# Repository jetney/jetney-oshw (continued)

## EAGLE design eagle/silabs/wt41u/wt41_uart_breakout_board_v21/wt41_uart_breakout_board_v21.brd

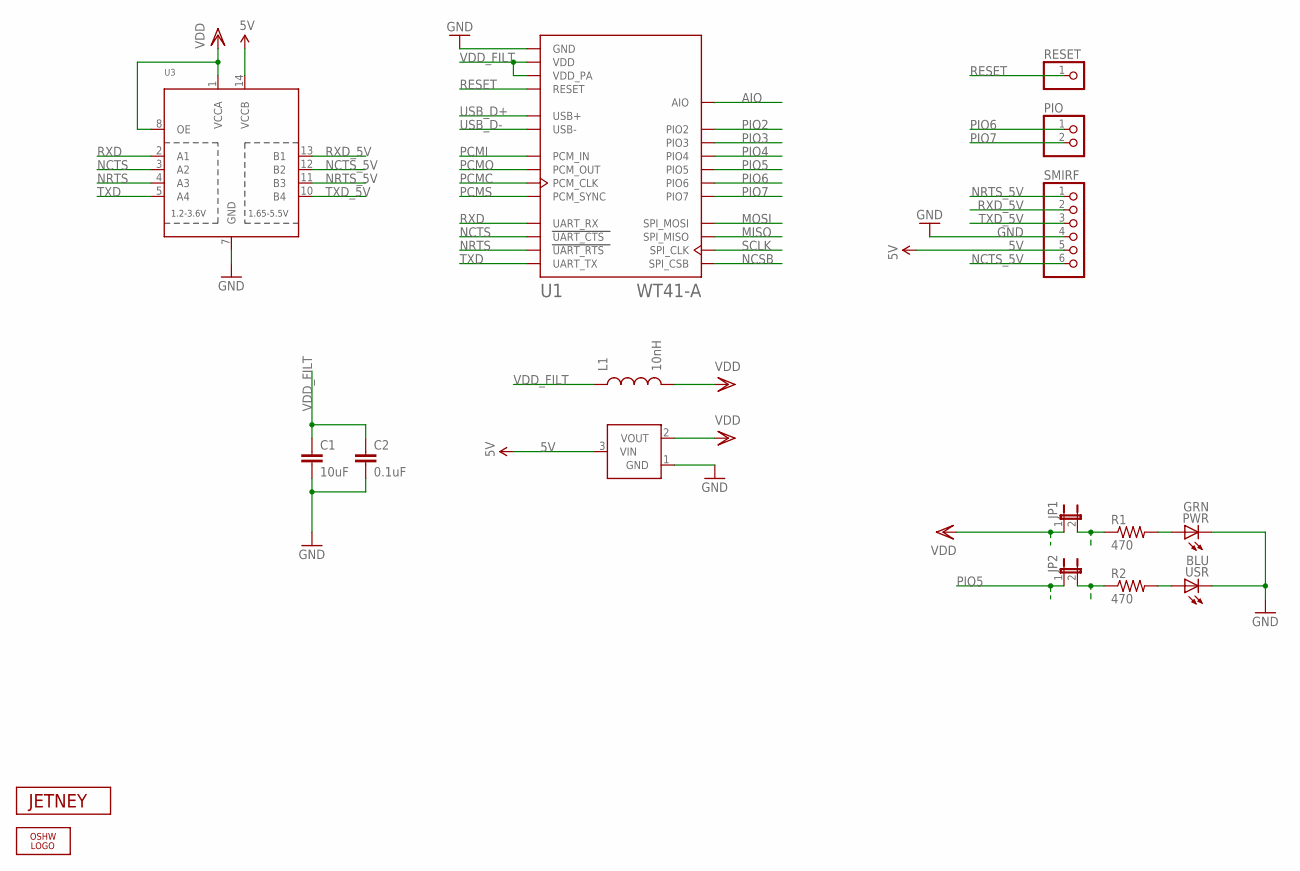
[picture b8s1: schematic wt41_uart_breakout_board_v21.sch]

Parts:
C1: 10uF; 0603-CAP
C2: 0.1uF; 0603-CAP
JP1, JP2: JUMPER-2SMD-NC; SJ_2S
L1: 10nH; 0603
LOGO1: OSHW_LOGO_FILLX0070-NT; OSHW_FILLX70_NOTEXT
PIO: PINHD-1X2; 1X02
PWR: GRN; CHIPLED_0805
R1, R2: 470; 0603-RES
RESET: PINHD-1X1; 1X01
SMIRF: PINHD-1X6; 1X06
U1: WT41-A
U2: MCP1700; SOT23-3
U3: TXB0104PWR; TSSOP14
U$4: JETNEY-LOGO-12
USR: BLU; CHIPLED_0805

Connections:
5V: SMIRF.5, U2.3 (VIN), U3.14 (VCCB)
AIO: U1.AIO
GND: C1.2, C2.2, PWR.C, SMIRF.4, U1.GND, U1.GND@2 (GND), U1.GND@3 (GND), U1.GND@4 (GND), U1.GND@5 (GND), U1.GND@6 (GND), U1.GND@7 (GND), U1.GND@8 (GND), U1.GND@9 (GND), U1.GND@10 (GND), U1.GND@11 (GND), U1.GND@12 (GND), U1.GND@13 (GND), U1.GND@14 (GND), U1.GND@15 (GND), U1.GND@16 (GND), U1.GND@17 (GND), U1.GND@18 (GND), U1.GND@19 (GND), U1.GND@20 (GND), U1.GND@21 (GND), U1.GND@22 (GND), U1.GND@23 (GND), U1.GND@24 (GND), U1.GND@25 (GND), U1.GND@26 (GND), U1.GND@27 (GND), U1.GND@28 (GND), U1.GND@29 (GND), U1.GND@30 (GND), U1.GND@31 (GND), U2.1 (GND), U3.7 (GND), USR.C
MISO: U1.SPI_MISO
MOSI: U1.SPI_MOSI
unnamed: PWR.A, R1.2
unnamed: R2.2, USR.A
unnamed: JP2.2, R2.1
NCSB: U1.SPI_CSB
NCTS: U1.UART_CTS, U3.3 (A2)
NCTS_5V: SMIRF.6, U3.12 (B2)
NRTS: U1.UART_RTS, U3.4 (A3)
NRTS_5V: SMIRF.1, U3.11 (B3)
PCMC: U1.PCM_CLK
PCMI: U1.PCM_IN
PCMO: U1.PCM_OUT
PCMS: U1.PCM_SYNC
PIO2: U1.PIO2
PIO3: U1.PIO3
PIO4: U1.PIO4
PIO5: JP2.1, U1.PIO5
PIO6: PIO.1, U1.PIO6
PIO7: PIO.2, U1.PIO7
RESET: RESET.1, U1.RESET
RXD: U1.UART_RX, U3.2 (A1)
RXD_5V: SMIRF.2, U3.13 (B1)
SCLK: U1.SPI_CLK
TXD: U1.UART_TX, U3.5 (A4)
TXD_5V: SMIRF.3, U3.10 (B4)
USB_D+: U1.USB+
USB_D-: U1.USB-
VDD: JP1.1, L1.2, U2.2 (VOUT), U3.1 (VCCA), U3.8 (OE)
VDDJP1: JP1.2, R1.1
VDD_FILT: C1.1, C2.1, L1.1, U1.VDD, U1.VDD_PA

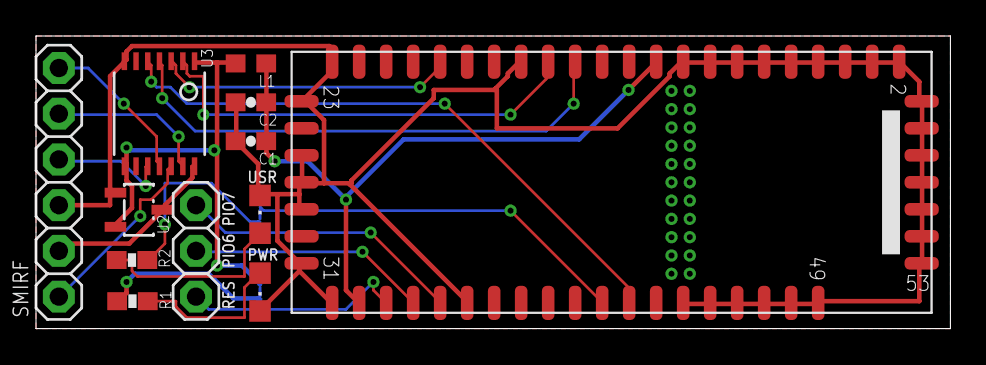
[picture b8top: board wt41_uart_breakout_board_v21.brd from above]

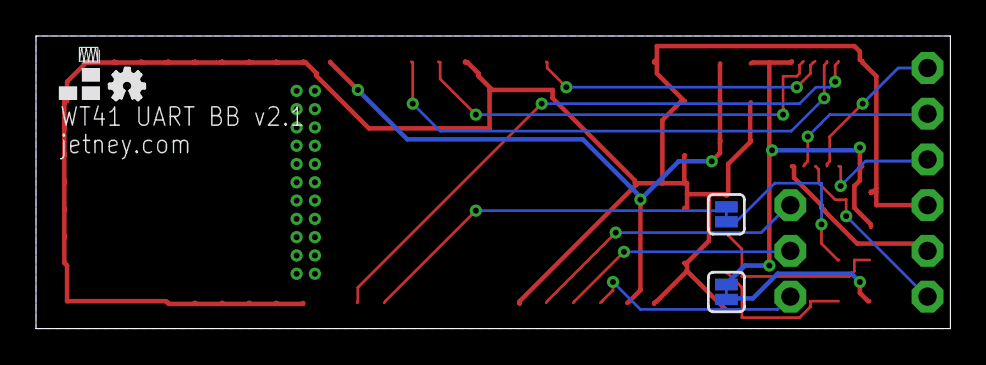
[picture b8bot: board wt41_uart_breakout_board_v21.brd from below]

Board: 2 copper layers, 50.8 x 16.3 mm, 17 parts (4 on the bottom side), 20 nets.

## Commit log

2017-07-16 Update license year
2017-07-16 Add .gitignore
2017-07-16 Commit all current breakout designs
2018-02-26 Correct invalid descriptions in many schematics
2018-02-26 Add WGM110 USB dongle v1.0 project
2018-02-26 Update .gitignore for private subfolders
2020-10-31 Add BGM113 breakout v1.0 schematic and layout PDFs
2020-10-31 Add BGM113 breakout v1.1 design files
